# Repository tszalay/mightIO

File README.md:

mightIO
=======

### What

The mightIO is an analog IO board capable of inputting and outputting voltages from -10V to +10V off of a +5V power supply, across four channels, without any external components.

### Why

The mightIO aims to solve the problem "I want to easily read or write analog voltages, in a wide range, decently fast, cheap, and with pretty good accuracy".

Every time I tell my fellow scientists about the Arduino, the first question they ask is "does it have analog outputs?" and I have a tough time explaining why the Arduino can't do it, but also why there aren't any straightforward shields that can do it.

There are shields for all sorts of crazy things, but it seems that analog output shields fall into two categories, either buffered audio output or voltage-limited DAC (eg. less than 0-5V). It's certainly possible to rig up split-rail power supplies and an opamp circuit, but that gets bulky and complicated quickly. 

My philosophy for using Arduino to save time is to "go from working to working", in other words, to be able to make incremental changes keeping everything functional, and this board embodies that much better than having to build I2C DAC + opamp combos from scratch every time.

### How

The +10V and -10V rails are generated using a MAX864 capacitive doubler/inverter chip, running at 180 kHz. The ADC is a MAX11612 and the DAC is a MCP4728, both 12-bit 4-channel I2C chips with range 0V-4.096V. The voltage scaling is performed using two quad TL064 low-power op-amps. The only connections to the Arduino board are +5V, GND, SDA, and SCL. In addition to the 4 inputs and 4 outputs, there is a +10V/GND/-10V breakout.

### Specs

All relevant numbers below are based on actual measurements.
* Footprint: 1.5 in x 1.25 in
* Est. materials cost: $8.90
* Voltage range: 2x Vin, minus about 0.6V droop
* Channels: 4 in, 4 out
* Noise: 40 mV pk-pk, <10 mV RMS (<0.1% noise)
* Resolution: 9 bits raw, 11 bits software median-filtered (<0.1% error)
* Power consumption: 20 mA (no load)
* Maximum effective output load: ~50 mA (3V droop)
* Output impedance: 50 ohms (<1.0V droop @ 1k load)
* Max # of devices: Up to 4 (but I2C addresses need to be reprogrammed) 

### Pricing

The BOM can be found in the repository under "Hardware" - unit cost is estimated at around $8.90 for a run of 1000, of which the ADC, DAC, and doubler each make up about 20%, respectively. This could probably be reduced by about 10% through careful tweaking of the part sourcing/values. Features could also be reduced (fewer channels, removing ADC), but I think the cost overhead is low enough that anyone wanting just an ADC or just a DAC would still buy the board.

I've heard that the retail markup is around 2x, so say the board sells for around $15-$20 - that's cheaper than or comparable to pretty much any other ADC -or- DAC solution out there, with the exception of the much more limited MCP4725 breakout.

### Market

The market for this is anyone that is using Arduinos to interface with a wide range of external devices/sensors/etc that require larger voltage inputs or outputs to function. The key is that it should be priced competitively enough that anyone looking for either a DAC or ADC would consider the board as the simplest and cheapest option.

### Software

The library isn't finished, but the basic parts are all there, just needs some other handy functions and examples. Other features I plan to add are getting the ADC set up in differential input mode to try low-noise measurements and a median-filtered analogRead.

### Who

[Tamas Szalay](http://tamas-szalay.squarespace.com/), full-time Applied Physics grad student and part-time hacker, Arduino afficionado

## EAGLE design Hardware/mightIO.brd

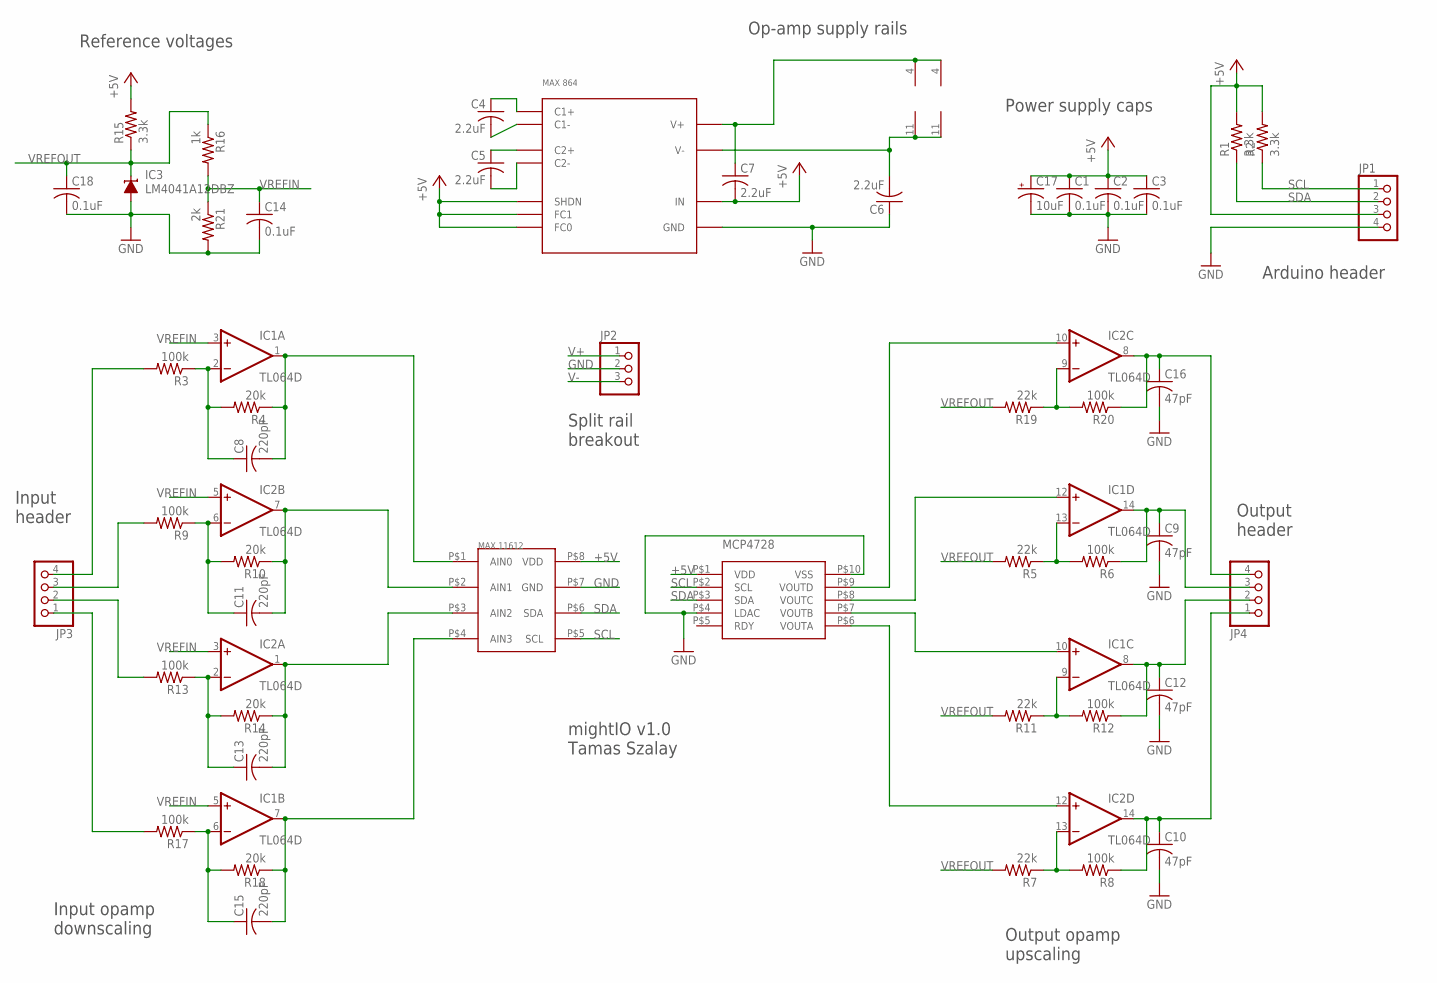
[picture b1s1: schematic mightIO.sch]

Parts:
C1, C2, C3, C14, C18: 0.1uF; C0603
C4, C5, C6, C7: 2.2uF; C0603
C8, C11, C13, C15: 220pF; C0603
C9, C10, C12, C16: 47pF; C0603
C17: 10uF; E2,5-6
IC1, IC2: TL064D; SO14
IC3: LM4041A12DBZ; DBZ_R-PDSO-G3
JP1, JP3, JP4: PINHD-1X4; 1X04
JP2: PINHD-1X3; 1X03
R1, R2, R15: 3.3k; R0603
R3, R6, R8, R9, R12, R13, R17, R20: 100k; R0603
R4, R10, R14, R18: 20k; R0603
R5, R7, R11, R19: 22k; R0603
R16: 1k; R0603
R21: 2k; R0603
U1: MAX11612
U$1: MAX864
U$2: MCP4728

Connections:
+5V: C1.1, C2.1, C3.1, C7.2, C17.+, JP1.3, R1.2, R2.2, R15.2, U1.P$8 (VDD), U$1.P$6 (SHDN), U$1.P$7 (FC1), U$1.P$8 (FC0), U$1.P$12 (IN), U$2.P$1 (VDD)
AI0: JP3.4, R3.2
AI1: JP3.3, R9.2
AI2: JP3.2, R13.2
AI3: JP3.1, R17.2
AOA: C10.1, IC2.14 (OUT), JP4.1, R8.1
AOB: C12.1, IC1.8 (OUT), JP4.2, R12.1
AOC: C9.1, IC1.14 (OUT), JP4.3, R6.1
AOD: C16.1, IC2.8 (OUT), JP4.4, R20.1
GND: C1.2, C2.2, C3.2, C6.1, C9.2, C10.2, C12.2, C14.2, C16.2, C17.-, C18.2, IC3.2 (A), JP1.4, JP2.2, R21.2, U1.P$7 (GND), U$1.P$3 (GND), U$1.P$11 (GND), U$2.P$4 (LDAC), U$2.P$10 (VSS)
unnamed: IC2.10 (+IN), U$2.P$9 (VOUTD)
unnamed: IC2.9 (-IN), R19.1, R20.2
unnamed: IC1.10 (+IN), U$2.P$7 (VOUTB)
unnamed: IC1.13 (-IN), R5.1, R6.2
unnamed: IC1.9 (-IN), R11.1, R12.2
unnamed: IC2.13 (-IN), R7.1, R8.2
unnamed: C4.1, U$1.P$16 (C1+)
unnamed: C4.2, U$1.P$1 (C1-)
unnamed: C5.1, U$1.P$2 (C2+)
unnamed: C5.2, U$1.P$4 (C2-)
unnamed: C8.1, IC1.2 (-IN), R3.1, R4.2
unnamed: C13.2, IC2.1 (OUT), R14.1, U1.P$3 (AIN2)
unnamed: C8.2, IC1.1 (OUT), R4.1, U1.P$1 (AIN0)
unnamed: C11.1, IC2.6 (-IN), R9.1, R10.2
unnamed: C11.2, IC2.7 (OUT), R10.1, U1.P$2 (AIN1)
unnamed: C15.2, IC1.7 (OUT), R18.1, U1.P$4 (AIN3)
unnamed: C13.1, IC2.2 (-IN), R13.1, R14.2
unnamed: IC2.12 (+IN), U$2.P$6 (VOUTA)
unnamed: C15.1, IC1.6 (-IN), R17.1, R18.2
unnamed: IC1.12 (+IN), U$2.P$8 (VOUTC)
SCL: JP1.1, R2.1, U1.P$5 (SCL), U$2.P$2 (SCL)
SDA: JP1.2, R1.1, U1.P$6 (SDA), U$2.P$3 (SDA)
V+: C7.1, IC1.4 (V+), IC2.4 (V+), JP2.1, U$1.P$15 (V+)
V-: C6.2, IC1.11 (V-), IC2.11 (V-), JP2.3, U$1.P$5 (V-)
VREFIN: C14.1, IC1.3 (+IN), IC1.5 (+IN), IC2.3 (+IN), IC2.5 (+IN), R16.2, R21.1
VREFOUT: C18.1, IC3.1 (C), R5.2, R7.2, R11.2, R15.1, R16.1, R19.2

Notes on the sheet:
Output header
Input header
Reference voltages
Input opamp downscaling
Output opamp upscaling
Arduino header
Power supply caps
Op-amp supply rails
mightIO v1.0 Tamas Szalay
Split rail breakout

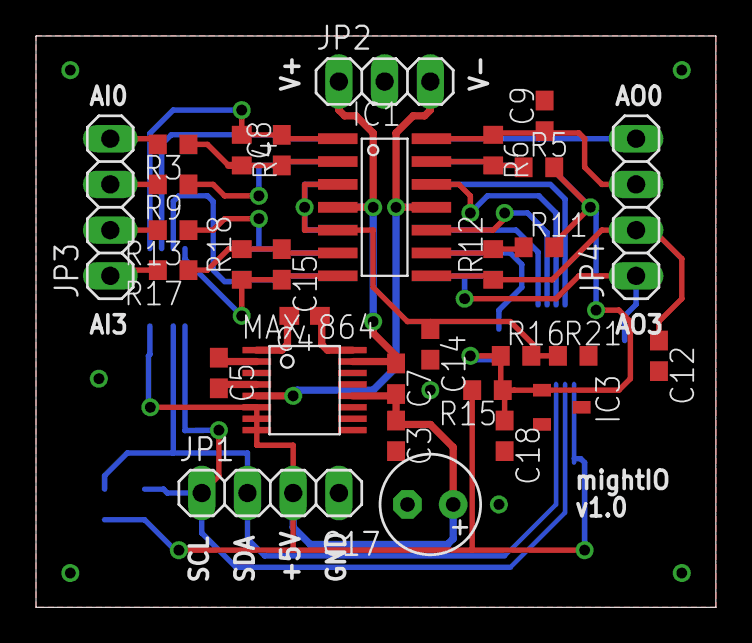
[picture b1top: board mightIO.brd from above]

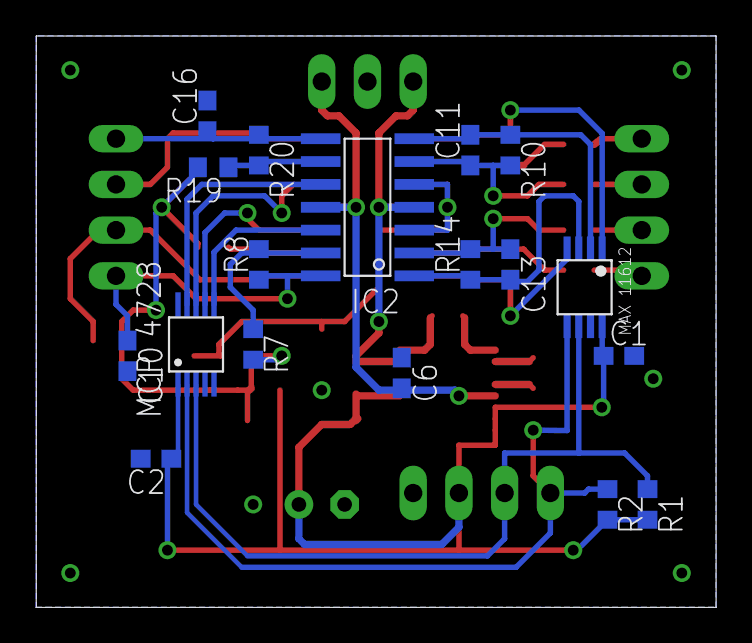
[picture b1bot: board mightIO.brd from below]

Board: 2 copper layers, 37.8 x 31.7 mm, 49 parts (18 on the bottom side), 36 nets.

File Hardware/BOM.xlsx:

Part | Qty | Digikey # | Unit Cost (10) | Unit Cost (1000) | Cost %
47pF | 4 | 1276-1037-1-ND | 0.03 | 6.3E-3 | 2.8338073213436295E-3
220pF | 4 | 1276-2237-1-ND | 0.03 | 7.62E-3 | 3.4275574267680089E-3
0.1uF | 5 | 399-1096-1-ND | 2.1999999999999999E-2 | 5.4000000000000003E-3 | 3.0362221300110318E-3
2.2uF | 4 | 587-1253-1-ND | 0.09 | 2.4750000000000001E-2 | 1.1132814476707116E-2
22uF | 1 | P16405CT-ND | 0.98899999999999999 | 0.58899999999999997 | 6.623462350283324E-2
1k | 1 | P1.0KYCT-ND | 0.83 | 0.14000000000000001 | 1.574337400746461E-2
2k | 1 | P2.0KYCT-ND | 0.62 | 0.11033 | 1.240690324459693E-2
3.3k | 3 | 311-3.3KGRCT-ND | 1.0999999999999999E-2 | 2.0400000000000001E-3 | 6.8821034946916723E-4
5.1k | 1 | P10KDBCT-ND | 0.62 | 7.6999999999999999E-2 | 8.6588557041055343E-3
10k | 1 | P10KDBCT-ND | 0.62 | 7.6999999999999999E-2 | 8.6588557041055343E-3
20k | 4 | P20KDBCT-ND | 0.62 | 4.2999999999999997E-2 | 1.9341859494885087E-2
22k | 4 | P22KDBCT-ND | 0.62 | 4.2999999999999997E-2 | 1.9341859494885087E-2
100k | 8 | P100KDBCT-ND | 0.43 | 4.2999999999999997E-2 | 3.8683718989770174E-2
LM4040 | 1 | LM4040AIM3-2.5/NOPBCT-ND | 1.76 | 0.82 | 9.2211190615149832E-2
MAX11612 | 1 | MAX11612EUA+-ND | 1.6719999999999999 | 1.657 | 0.18633407664549181
MAX864 | 1 | MAX864EEE+-ND | 3.762 | 1.6830000000000001 | 0.18925784610402097
MCP4728 | 1 | MCP4728A0-E/UN-ND | 1.89 | 1.44 | 0.16193184693392168
TL064 | 2 | 296-14992-1-ND | 0.499 | 0.21174999999999999 | 4.7623706372580434E-2
Board (est.) | 1 |  | 1 | 1 | 0.11245267148189006
Total cost |  |  | 23.904 | 8.8926300000000005

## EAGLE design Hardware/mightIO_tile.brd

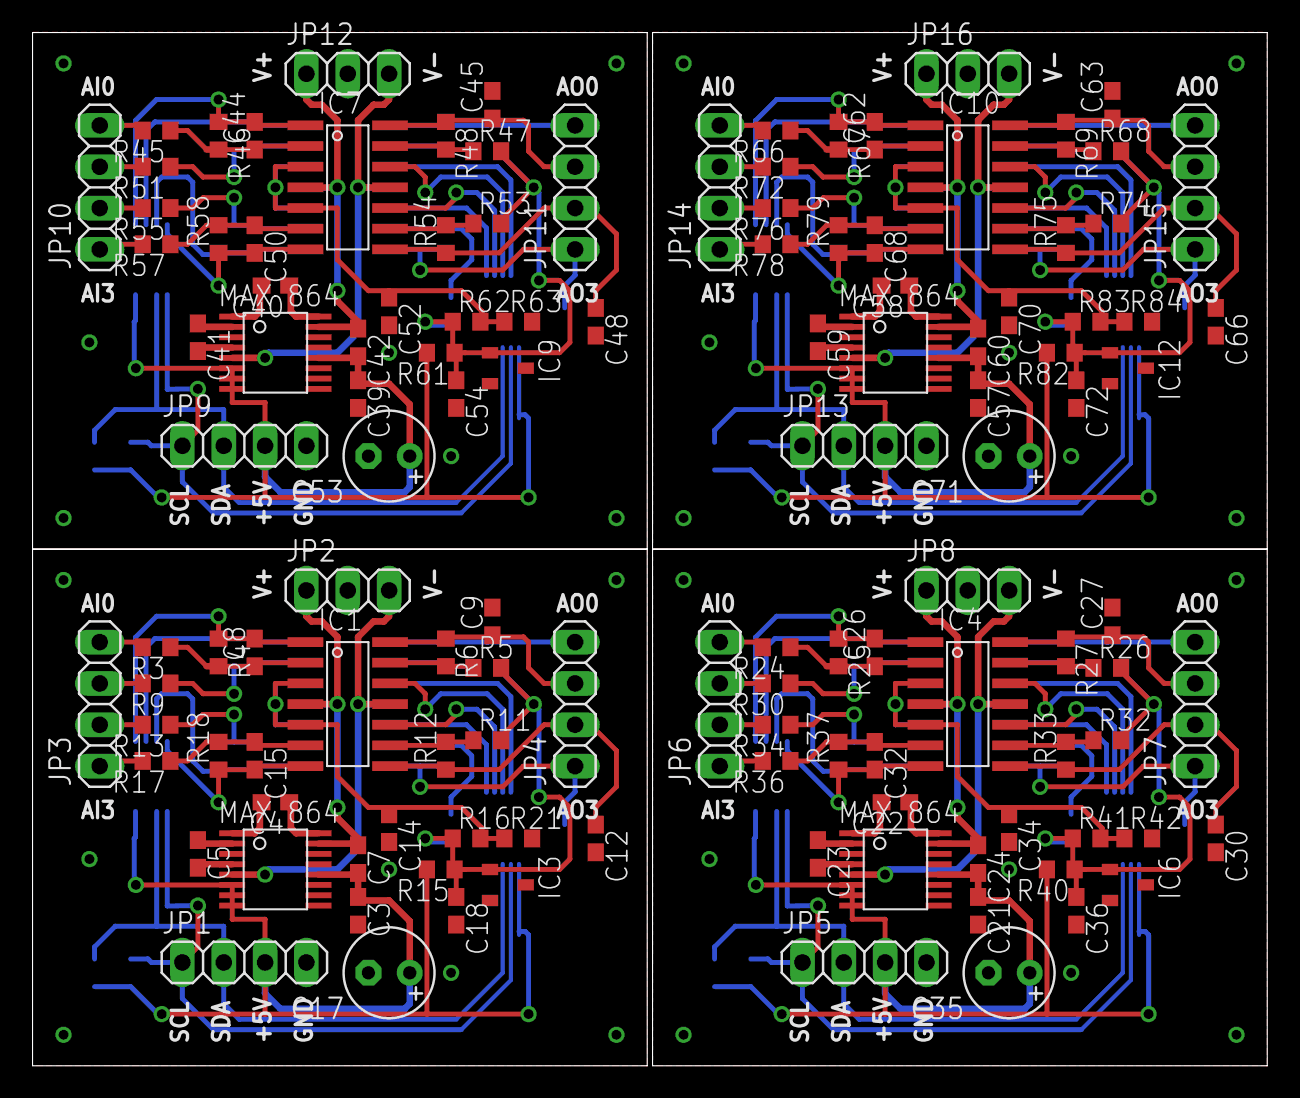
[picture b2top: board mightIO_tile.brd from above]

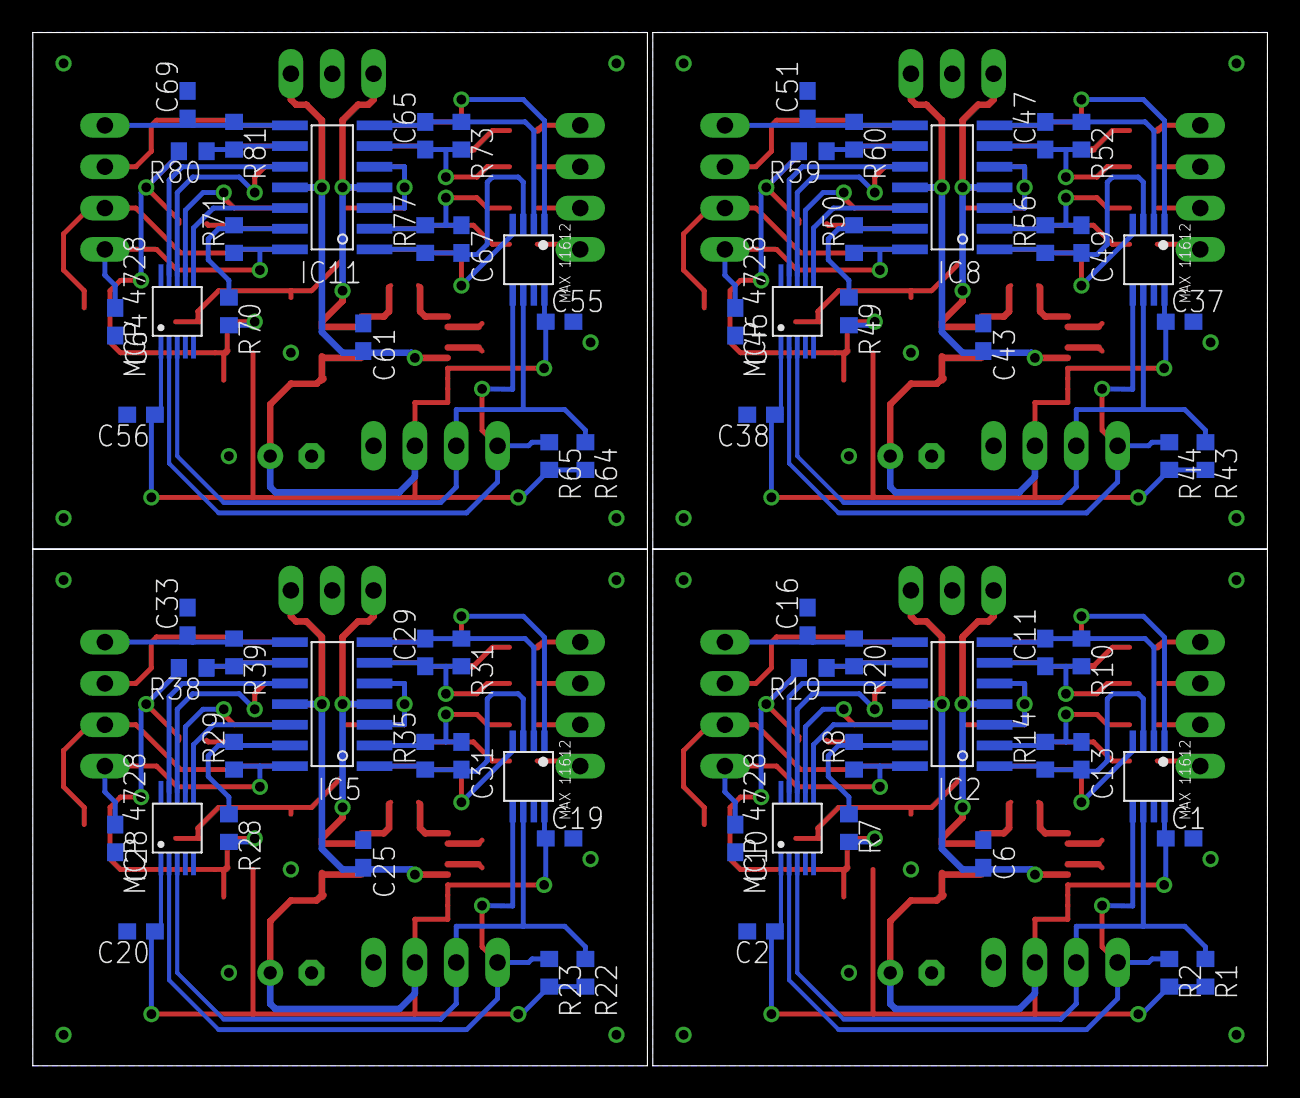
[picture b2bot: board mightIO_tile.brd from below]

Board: 2 copper layers, 75.9 x 63.5 mm, 196 parts (72 on the bottom side), 144 nets.

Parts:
C1, C2, C3, C14, C18, C19, C20, C21, C34, C36, C37, C38, C39, C52, C54, C55, C56, C57, C70, C72: 0.1uF; C0603
C4, C5, C6, C7, C22, C23, C24, C25, C40, C41, C42, C43, C58, C59, C60, C61: 2.2uF; C0603
C8, C11, C13, C15, C26, C29, C31, C32, C44, C47, C49, C50, C62, C65, C67, C68: 220pF; C0603
C9, C10, C12, C16, C27, C28, C30, C33, C45, C46, C48, C51, C63, C64, C66, C69: 47pF; C0603
C17, C35, C53, C71: 10uF; E2,5-6
IC1, IC2, IC4, IC5, IC7, IC8, IC10, IC11: TL064D; SO14
IC3, IC6, IC9, IC12: LM4041A12DBZ; DBZ_R-PDSO-G3
JP1, JP3, JP4, JP5, JP6, JP7, JP9, JP10, JP11, JP13, JP14, JP15: 1X04
JP2, JP8, JP12, JP16: 1X03
R1, R2, R15, R22, R23, R40, R43, R44, R61, R64, R65, R82: 3.3k; R0603
R3, R6, R8, R9, R12, R13, R17, R20, R24, R27, R29, R30, R33, R34, R36, R39, R45, R48, R50, R51, R54, R55, R57, R60, R66, R69, R71, R72, R75, R76, R78, R81: 100k; R0603
R4, R10, R14, R18, R25, R31, R35, R37, R46, R52, R56, R58, R67, R73, R77, R79: 20k; R0603
R5, R7, R11, R19, R26, R28, R32, R38, R47, R49, R53, R59, R68, R70, R74, R80: 22k; R0603
R16, R41, R62, R83: 1k; R0603
R21, R42, R63, R84: 5.1k; R0603
U1, U2, U3, U4: MAX11612
U$1, U$3, U$5, U$7: MAX864
U$2, U$4, U$6, U$8: MCP4728

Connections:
+5V: C1.1, C2.1, C3.1, C7.2, C17.+, JP1.3, R1.2, R2.2, R15.2, U1.P$8, U$1.P$6, U$1.P$7, U$1.P$8, U$1.P$12, U$2.P$1
+5V1: C19.1, C20.1, C21.1, C24.2, C35.+, JP5.3, R22.2, R23.2, R40.2, U2.P$8, U$3.P$6, U$3.P$7, U$3.P$8, U$3.P$12, U$4.P$1
+5V2: C37.1, C38.1, C39.1, C42.2, C53.+, JP9.3, R43.2, R44.2, R61.2, U3.P$8, U$5.P$6, U$5.P$7, U$5.P$8, U$5.P$12, U$6.P$1
+5V3: C55.1, C56.1, C57.1, C60.2, C71.+, JP13.3, R64.2, R65.2, R82.2, U4.P$8, U$7.P$6, U$7.P$7, U$7.P$8, U$7.P$12, U$8.P$1
AI0: JP3.4, R3.2
AI1: JP3.3, R9.2
AI2: JP3.2, R13.2
AI3: JP3.1, R17.2
AI4: JP6.3, R30.2
AI5: JP6.4, R24.2
AI6: JP6.1, R36.2
AI7: JP6.2, R34.2
AI8: JP10.3, R51.2
AI9: JP10.4, R45.2
AI10: JP10.1, R57.2
AI11: JP10.2, R55.2
AI12: JP14.3, R72.2
AI13: JP14.4, R66.2
AI14: JP14.1, R78.2
AI15: JP14.2, R76.2
AOA: C10.1, IC2.14, JP4.1, R8.1
AOA1: C28.1, IC5.14, JP7.1, R29.1
AOA2: C46.1, IC8.14, JP11.1, R50.1
AOA3: C64.1, IC11.14, JP15.1, R71.1
AOB: C12.1, IC1.8, JP4.2, R12.1
AOB1: C30.1, IC4.8, JP7.2, R33.1
AOB2: C48.1, IC7.8, JP11.2, R54.1
AOB3: C66.1, IC10.8, JP15.2, R75.1
AOC: C9.1, IC1.14, JP4.3, R6.1
AOC1: C27.1, IC4.14, JP7.3, R27.1
AOC2: C45.1, IC7.14, JP11.3, R48.1
AOC3: C63.1, IC10.14, JP15.3, R69.1
AOD: C16.1, IC2.8, JP4.4, R20.1
AOD1: C33.1, IC5.8, JP7.4, R39.1
AOD2: C51.1, IC8.8, JP11.4, R60.1
AOD3: C69.1, IC11.8, JP15.4, R81.1
GND: C1.2, C2.2, C3.2, C6.1, C9.2, C10.2, C12.2, C14.2, C16.2, C17.-, C18.2, IC3.2, JP1.4, JP2.2, R21.2, U1.P$7, U$1.P$3, U$1.P$11, U$2.P$4, U$2.P$10
GND1: C19.2, C20.2, C21.2, C25.1, C27.2, C28.2, C30.2, C33.2, C34.2, C35.-, C36.2, IC6.2, JP5.4, JP8.2, R42.2, U2.P$7, U$3.P$3, U$3.P$11, U$4.P$4, U$4.P$10
GND2: C37.2, C38.2, C39.2, C43.1, C45.2, C46.2, C48.2, C51.2, C52.2, C53.-, C54.2, IC9.2, JP9.4, JP12.2, R63.2, U3.P$7, U$5.P$3, U$5.P$11, U$6.P$4, U$6.P$10
GND3: C55.2, C56.2, C57.2, C61.1, C63.2, C64.2, C66.2, C69.2, C70.2, C71.-, C72.2, IC12.2, JP13.4, JP16.2, R84.2, U4.P$7, U$7.P$3, U$7.P$11, U$8.P$4, U$8.P$10
unnamed: IC2.10, U$2.P$9
unnamed: IC2.9, R19.1, R20.2
unnamed: IC1.10, U$2.P$7
unnamed: IC1.13, R5.1, R6.2
unnamed: IC1.9, R11.1, R12.2
unnamed: IC2.13, R7.1, R8.2
unnamed: C4.1, U$1.P$16
unnamed: C4.2, U$1.P$1
unnamed: C5.1, U$1.P$2
unnamed: C5.2, U$1.P$4
unnamed: C8.1, IC1.2, R3.1, R4.2
unnamed: C13.2, IC2.1, R14.1, U1.P$3
unnamed: IC5.10, U$4.P$9
unnamed: C22.1, U$3.P$16
unnamed: C22.2, U$3.P$1
unnamed: C23.1, U$3.P$2
unnamed: C23.2, U$3.P$4
unnamed: C8.2, IC1.1, R4.1, U1.P$1
unnamed: C11.1, IC2.6, R9.1, R10.2
unnamed: C11.2, IC2.7, R10.1, U1.P$2
unnamed: C26.1, IC4.2, R24.1, R25.2
unnamed: C15.2, IC1.7, R18.1, U1.P$4
unnamed: C13.1, IC2.2, R13.1, R14.2
unnamed: C29.1, IC5.6, R30.1, R31.2
unnamed: IC2.12, U$2.P$6
unnamed: C31.1, IC5.2, R34.1, R35.2
unnamed: C15.1, IC1.6, R17.1, R18.2
unnamed: C32.1, IC4.6, R36.1, R37.2
unnamed: IC4.12, U$4.P$8
unnamed: C29.2, IC5.7, R31.1, U2.P$2
unnamed: IC4.10, U$4.P$7
unnamed: C26.2, IC4.1, R25.1, U2.P$1
unnamed: C31.2, IC5.1, R35.1, U2.P$3
unnamed: IC1.12, U$2.P$8
unnamed: C32.2, IC4.7, R37.1, U2.P$4
unnamed: IC5.12, U$4.P$6
unnamed: IC5.9, R38.1, R39.2
unnamed: IC4.13, R26.1, R27.2
unnamed: IC4.9, R32.1, R33.2
unnamed: IC5.13, R28.1, R29.2
unnamed: IC8.10, U$6.P$9
unnamed: C40.1, U$5.P$16
unnamed: C40.2, U$5.P$1
unnamed: C41.1, U$5.P$2
unnamed: C41.2, U$5.P$4
unnamed: C44.1, IC7.2, R45.1, R46.2
unnamed: C47.1, IC8.6, R51.1, R52.2
unnamed: C49.1, IC8.2, R55.1, R56.2
unnamed: C50.1, IC7.6, R57.1, R58.2
unnamed: IC7.12, U$6.P$8
unnamed: C47.2, IC8.7, R52.1, U3.P$2
unnamed: IC7.10, U$6.P$7
unnamed: C44.2, IC7.1, R46.1, U3.P$1
unnamed: C49.2, IC8.1, R56.1, U3.P$3
unnamed: C50.2, IC7.7, R58.1, U3.P$4
unnamed: IC8.12, U$6.P$6
unnamed: IC8.9, R59.1, R60.2
unnamed: IC7.13, R47.1, R48.2
unnamed: IC7.9, R53.1, R54.2
unnamed: IC8.13, R49.1, R50.2
unnamed: IC11.10, U$8.P$9
unnamed: C58.1, U$7.P$16
unnamed: C58.2, U$7.P$1
unnamed: C59.1, U$7.P$2
unnamed: C59.2, U$7.P$4
unnamed: C62.1, IC10.2, R66.1, R67.2
unnamed: C65.1, IC11.6, R72.1, R73.2
unnamed: C67.1, IC11.2, R76.1, R77.2
unnamed: C68.1, IC10.6, R78.1, R79.2
unnamed: IC10.12, U$8.P$8
unnamed: C65.2, IC11.7, R73.1, U4.P$2
unnamed: IC10.10, U$8.P$7
unnamed: C62.2, IC10.1, R67.1, U4.P$1
unnamed: C67.2, IC11.1, R77.1, U4.P$3
unnamed: C68.2, IC10.7, R79.1, U4.P$4
unnamed: IC11.12, U$8.P$6
unnamed: IC11.9, R80.1, R81.2
unnamed: IC10.13, R68.1, R69.2
unnamed: IC10.9, R74.1, R75.2
unnamed: IC11.13, R70.1, R71.2
SCL: JP1.1, R2.1, U1.P$5, U$2.P$2
SCL1: JP5.1, R23.1, U2.P$5, U$4.P$2
SCL2: JP9.1, R44.1, U3.P$5, U$6.P$2
SCL3: JP13.1, R65.1, U4.P$5, U$8.P$2
SDA: JP1.2, R1.1, U1.P$6, U$2.P$3
SDA1: JP5.2, R22.1, U2.P$6, U$4.P$3
SDA2: JP9.2, R43.1, U3.P$6, U$6.P$3
SDA3: JP13.2, R64.1, U4.P$6, U$8.P$3
V+: C7.1, IC1.4, IC2.4, JP2.1, U$1.P$15
V+1: C24.1, IC4.4, IC5.4, JP8.1, U$3.P$15
V+2: C42.1, IC7.4, IC8.4, JP12.1, U$5.P$15
V+3: C60.1, IC10.4, IC11.4, JP16.1, U$7.P$15
V-: C6.2, IC1.11, IC2.11, JP2.3, U$1.P$5
V-1: C25.2, IC4.11, IC5.11, JP8.3, U$3.P$5
V-2: C43.2, IC7.11, IC8.11, JP12.3, U$5.P$5
V-3: C61.2, IC10.11, IC11.11, JP16.3, U$7.P$5
VREFIN: C14.1, IC1.3, IC1.5, IC2.3, IC2.5, R16.2, R21.1
VREFIN1: C34.1, IC4.3, IC4.5, IC5.3, IC5.5, R41.2, R42.1
VREFIN2: C52.1, IC7.3, IC7.5, IC8.3, IC8.5, R62.2, R63.1
VREFIN3: C70.1, IC10.3, IC10.5, IC11.3, IC11.5, R83.2, R84.1
VREFOUT: C18.1, IC3.1, R5.2, R7.2, R11.2, R15.1, R16.1, R19.2
VREFOUT1: C36.1, IC6.1, R26.2, R28.2, R32.2, R38.2, R40.1, R41.1
VREFOUT2: C54.1, IC9.1, R47.2, R49.2, R53.2, R59.2, R61.1, R62.1
VREFOUT3: C72.1, IC12.1, R68.2, R70.2, R74.2, R80.2, R82.1, R83.1

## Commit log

2014-05-17 Actually works now
2014-07-15 Some part value updates
2014-07-30 Some routing updates, more needed
2014-09-18 Layout tweaks, added cap
2014-09-18 Added silkscreen, ready to go
2014-09-19 Gerber files done
2014-09-23 Added aluminum polymer to BOM
2014-10-12 Library updates
2014-10-13 Switched output amplifiers to non-inverting
2014-10-15 Touched up silkscreen, moved caps
2014-10-15 BOM updates, added 1% calculation
2014-10-15 Something changed?
2014-10-16 Updated tiled board
2014-11-17 BOM updates
2014-11-17 Added pdf schematic
2015-04-22 Example fixes
2015-04-22 Channels correctly reversed
2016-03-10 Adding some calibration ability
2016-03-10 Fixed up previous bugs in offsets
2016-05-09 Annotated schematic and labeled board
